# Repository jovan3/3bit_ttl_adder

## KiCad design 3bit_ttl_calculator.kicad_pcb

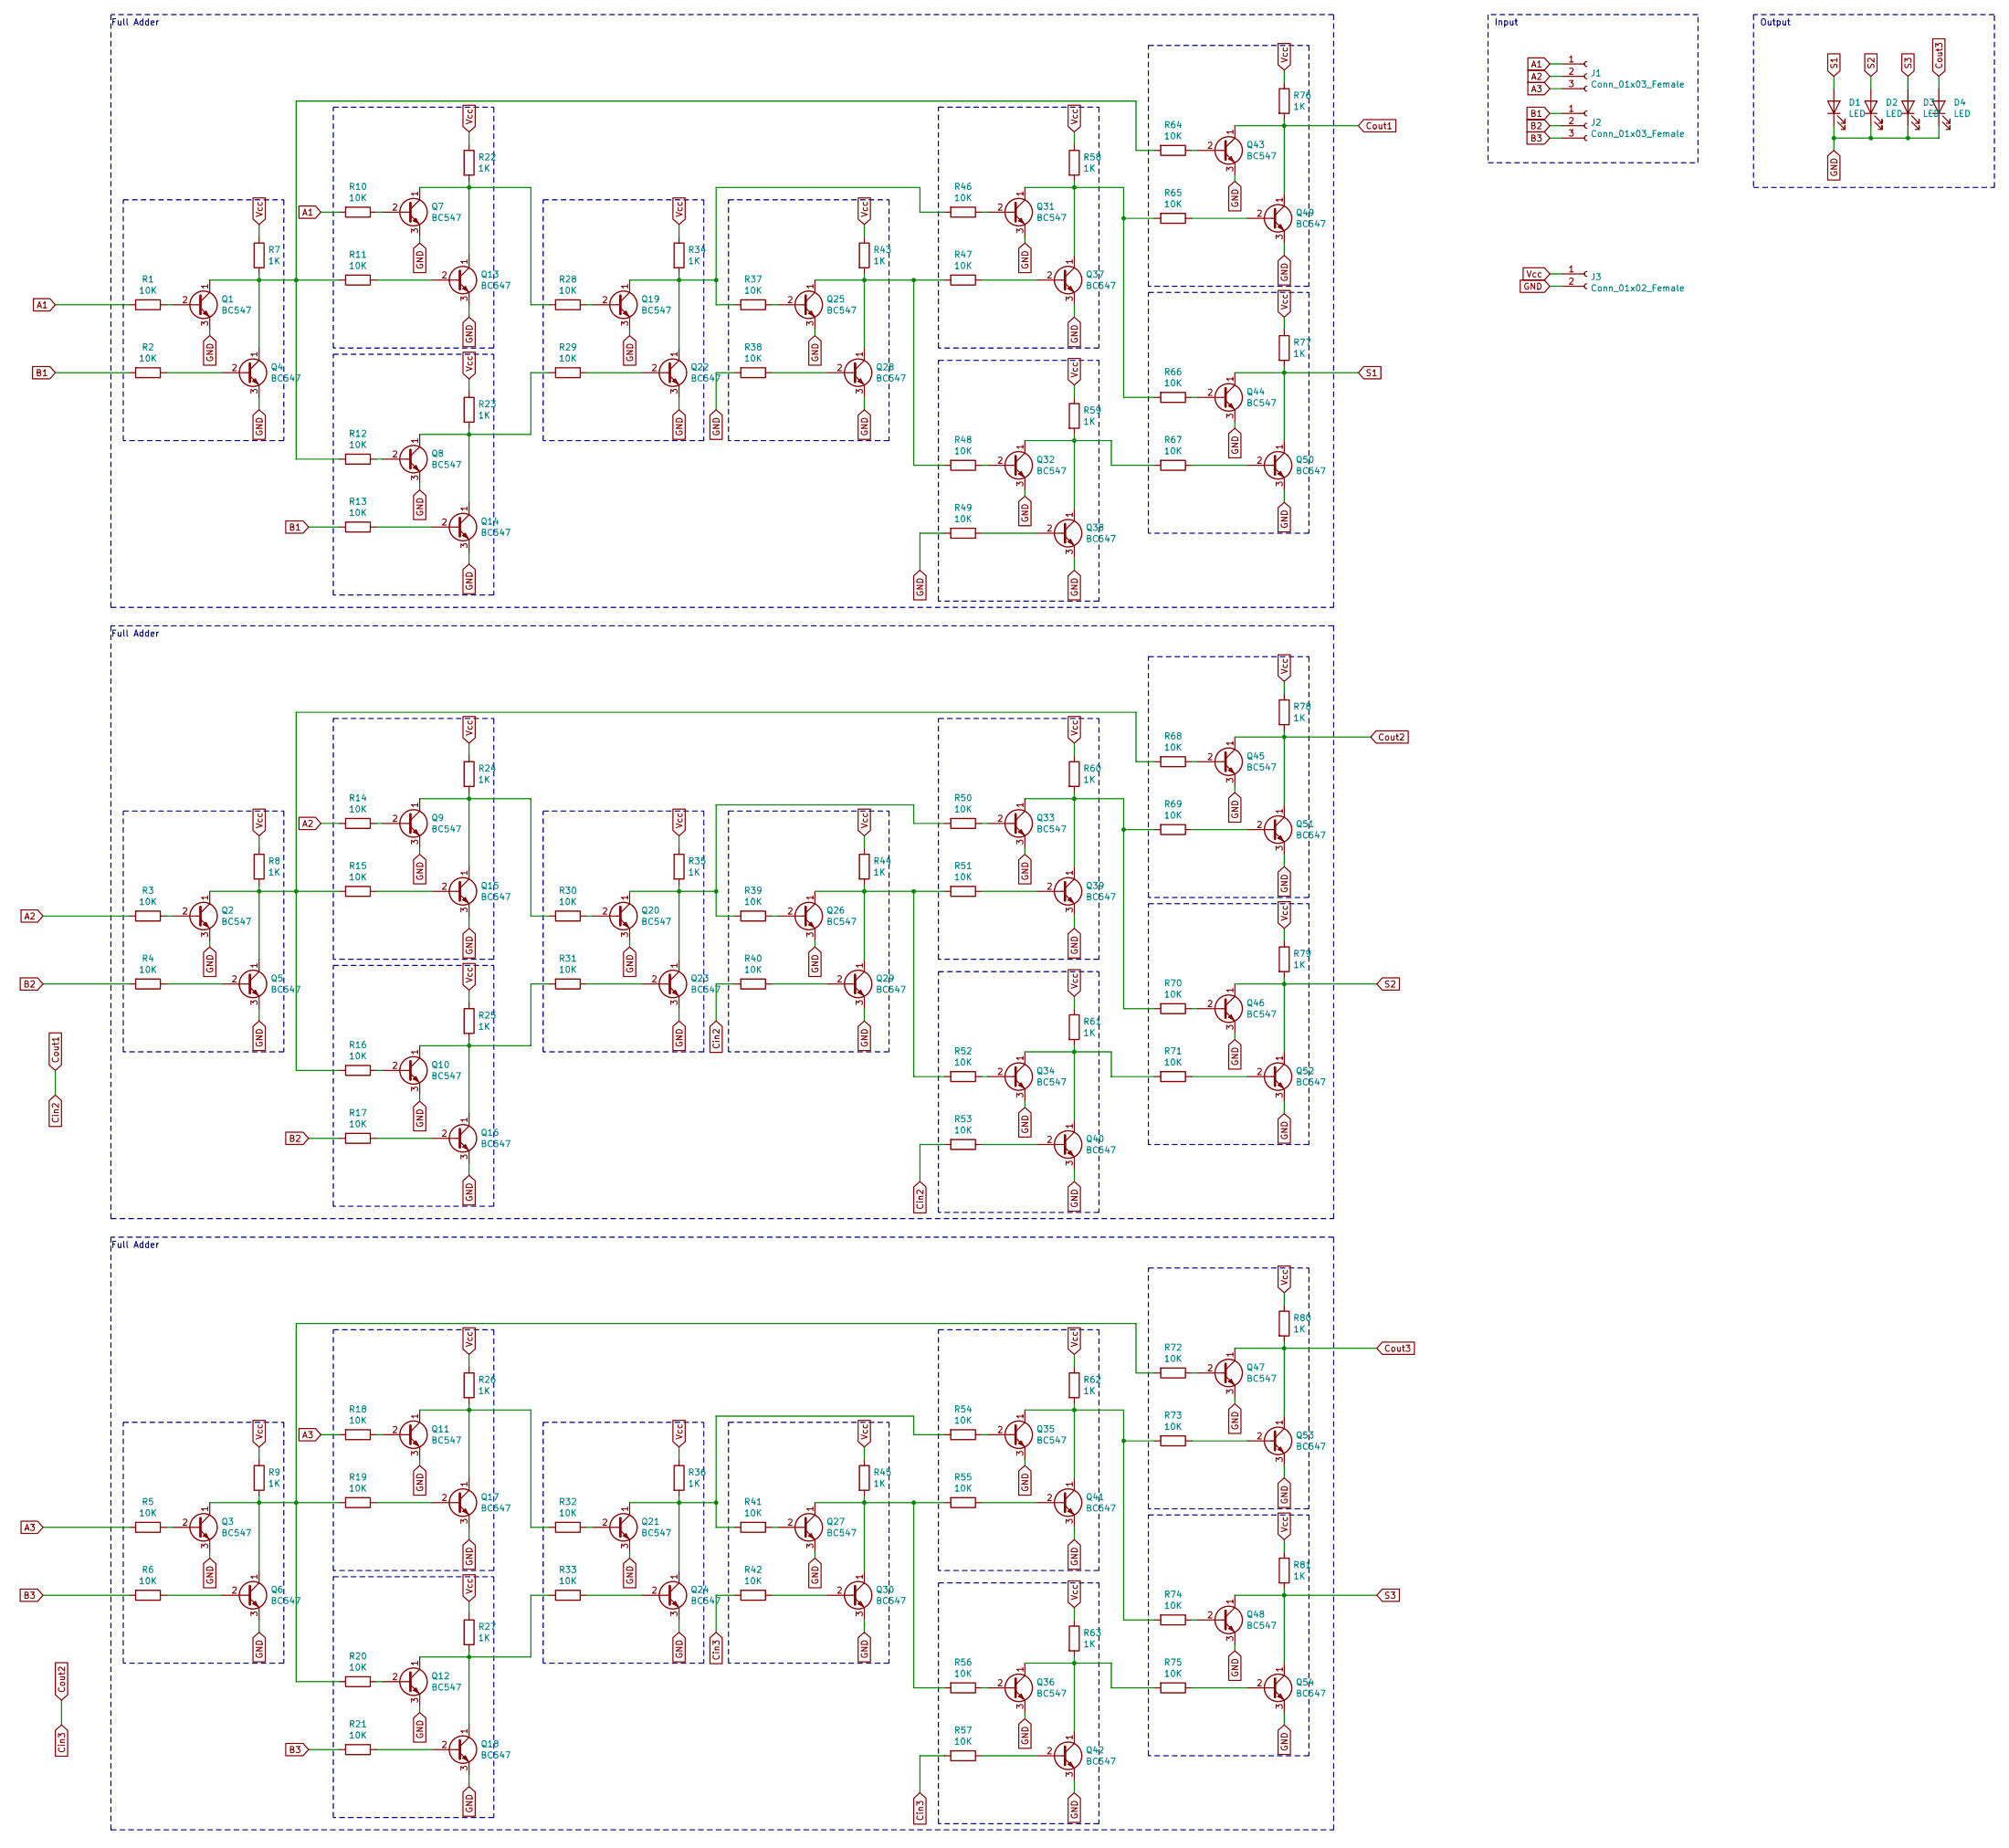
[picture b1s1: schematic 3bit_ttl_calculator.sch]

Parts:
D1, D2, D3, D4: LED; LED_D3.0mm
J1, J2: Conn_01x03_Female; PinHeader_1x03_P2.54mm_Vertical
J3: Conn_01x02_Female; PinHeader_1x02_P2.54mm_Vertical
Q1, Q2, Q3, Q4, Q5, Q6, Q7, Q8, Q9, Q10, Q11, Q12, Q13, Q14, Q15, Q16, Q17, Q18, Q19, Q20, Q21, Q22, Q23, Q24, Q25, Q26, Q27, Q28, Q29, Q30, Q31, Q32, Q33, Q34, Q35, Q36, Q37, Q38, Q39, Q40, Q41, Q42, Q43, Q44, Q45, Q46, Q47, Q48, Q49, Q50, Q51, Q52, Q53, Q54: BC547; TO-92_Inline
R1, R2, R3, R4, R5, R6, R10, R11, R12, R13, R14, R15, R16, R17, R18, R19, R20, R21, R28, R29, R30, R31, R32, R33, R37, R38, R39, R40, R41, R42, R46, R47, R48, R49, R50, R51, R52, R53, R54, R55, R56, R57, R64, R65, R66, R67, R68, R69, R70, R71, R72, R73, R74, R75: 10K; R_Axial_DIN0207_L6.3mm_D2.5mm_P10.16mm_Horizontal
R7, R8, R9, R22, R23, R24, R25, R26, R27, R34, R35, R36, R43, R44, R45, R58, R59, R60, R61, R62, R63, R76, R77, R78, R79, R80, R81: 1K; R_Axial_DIN0207_L6.3mm_D2.5mm_P10.16mm_Horizontal

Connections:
A1: J1.1, R1.2, R10.2
A2: J1.2, R3.2, R14.2
A3: J1.3, R5.2, R18.2
B1: J2.1, R2.2, R13.2
B2: J2.2, R4.2, R17.2
B3: J2.3, R6.2, R21.2
Cin2: Q43.1 (C), Q49.1 (C), R40.2, R53.2, R76.2
Cin3: Q45.1 (C), Q51.1 (C), R42.2, R57.2, R78.2
Cout3: D4.2 (A), Q47.1 (C), Q53.1 (C), R80.2
GND: D1.1 (K), D2.1 (K), D3.1 (K), D4.1 (K), J3.2, Q1.3 (E), Q2.3 (E), Q3.3 (E), Q4.3 (E), Q5.3 (E), Q6.3 (E), Q7.3 (E), Q8.3 (E), Q9.3 (E), Q10.3 (E), Q11.3 (E), Q12.3 (E), Q13.3 (E), Q14.3 (E), Q15.3 (E), Q16.3 (E), Q17.3 (E), Q18.3 (E), Q19.3 (E), Q20.3 (E), Q21.3 (E), Q22.3 (E), Q23.3 (E), Q24.3 (E), Q25.3 (E), Q26.3 (E), Q27.3 (E), Q28.3 (E), Q29.3 (E), Q30.3 (E), Q31.3 (E), Q32.3 (E), Q33.3 (E), Q34.3 (E), Q35.3 (E), Q36.3 (E), Q37.3 (E), Q38.3 (E), Q39.3 (E), Q40.3 (E), Q41.3 (E), Q42.3 (E), Q43.3 (E), Q44.3 (E), Q45.3 (E), Q46.3 (E), Q47.3 (E), Q48.3 (E), Q49.3 (E), Q50.3 (E), Q51.3 (E), Q52.3 (E), Q53.3 (E), Q54.3 (E), R38.2, R49.2
unnamed: Q1.1 (C), Q4.1 (C), R7.2, R11.2, R12.2, R64.2
unnamed: Q1.2 (B), R1.1
unnamed: Q2.1 (C), Q5.1 (C), R8.2, R15.2, R16.2, R68.2
unnamed: Q2.2 (B), R3.1
unnamed: Q3.1 (C), Q6.1 (C), R9.2, R19.2, R20.2, R72.2
unnamed: Q3.2 (B), R5.1
unnamed: Q4.2 (B), R2.1
unnamed: Q5.2 (B), R4.1
unnamed: Q6.2 (B), R6.1
unnamed: Q7.2 (B), R10.1
unnamed: Q8.2 (B), R12.1
unnamed: Q9.2 (B), R14.1
unnamed: Q10.1 (C), Q16.1 (C), R25.2, R31.2
unnamed: Q10.2 (B), R16.1
unnamed: Q11.1 (C), Q17.1 (C), R26.2, R32.2
unnamed: Q11.2 (B), R18.1
unnamed: Q12.1 (C), Q18.1 (C), R27.2, R33.2
unnamed: Q12.2 (B), R20.1
unnamed: Q7.1 (C), Q13.1 (C), R22.2, R28.2
unnamed: Q13.2 (B), R11.1
unnamed: Q8.1 (C), Q14.1 (C), R23.2, R29.2
unnamed: Q14.2 (B), R13.1
unnamed: Q9.1 (C), Q15.1 (C), R24.2, R30.2
unnamed: Q15.2 (B), R15.1
unnamed: Q16.2 (B), R17.1
unnamed: Q17.2 (B), R19.1
unnamed: Q18.2 (B), R21.1
unnamed: Q19.1 (C), Q22.1 (C), R34.2, R37.2, R46.2
unnamed: Q19.2 (B), R28.1
unnamed: Q20.1 (C), Q23.1 (C), R35.2, R39.2, R50.2
unnamed: Q20.2 (B), R30.1
unnamed: Q21.1 (C), Q24.1 (C), R36.2, R41.2, R54.2
unnamed: Q21.2 (B), R32.1
unnamed: Q22.2 (B), R29.1
unnamed: Q23.2 (B), R31.1
unnamed: Q24.2 (B), R33.1
unnamed: Q25.1 (C), Q28.1 (C), R43.2, R47.2, R48.2
unnamed: Q25.2 (B), R37.1
unnamed: Q26.1 (C), Q29.1 (C), R44.2, R51.2, R52.2
unnamed: Q26.2 (B), R39.1
unnamed: Q27.1 (C), Q30.1 (C), R45.2, R55.2, R56.2
unnamed: Q27.2 (B), R41.1
unnamed: Q28.2 (B), R38.1
unnamed: Q29.2 (B), R40.1
unnamed: Q30.2 (B), R42.1
unnamed: Q31.1 (C), Q37.1 (C), R58.2, R65.2, R66.2
unnamed: Q31.2 (B), R46.1
unnamed: Q32.1 (C), Q38.1 (C), R59.2, R67.2
unnamed: Q32.2 (B), R48.1
unnamed: Q33.1 (C), Q39.1 (C), R60.2, R69.2, R70.2
unnamed: Q33.2 (B), R50.1
unnamed: Q34.1 (C), Q40.1 (C), R61.2, R71.2
unnamed: Q34.2 (B), R52.1
unnamed: Q35.1 (C), Q41.1 (C), R62.2, R73.2, R74.2
unnamed: Q35.2 (B), R54.1
unnamed: Q36.1 (C), Q42.1 (C), R63.2, R75.2
unnamed: Q36.2 (B), R56.1
unnamed: Q37.2 (B), R47.1
unnamed: Q38.2 (B), R49.1
unnamed: Q39.2 (B), R51.1
unnamed: Q40.2 (B), R53.1
unnamed: Q41.2 (B), R55.1
unnamed: Q42.2 (B), R57.1
unnamed: Q43.2 (B), R64.1
unnamed: Q44.2 (B), R66.1
unnamed: Q45.2 (B), R68.1
unnamed: Q46.2 (B), R70.1
unnamed: Q47.2 (B), R72.1
unnamed: Q48.2 (B), R74.1
unnamed: Q49.2 (B), R65.1
unnamed: Q50.2 (B), R67.1
unnamed: Q51.2 (B), R69.1
unnamed: Q52.2 (B), R71.1
unnamed: Q53.2 (B), R73.1
unnamed: Q54.2 (B), R75.1
S1: D1.2 (A), Q44.1 (C), Q50.1 (C), R77.2
S2: D2.2 (A), Q46.1 (C), Q52.1 (C), R79.2
S3: D3.2 (A), Q48.1 (C), Q54.1 (C), R81.2
Vcc: J3.1, R7.1, R8.1, R9.1, R22.1, R23.1, R24.1, R25.1, R26.1, R27.1, R34.1, R35.1, R36.1, R43.1, R44.1, R45.1, R58.1, R59.1, R60.1, R61.1, R62.1, R63.1, R76.1, R77.1, R78.1, R79.1, R80.1, R81.1

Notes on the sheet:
Full Adder
Output
Input

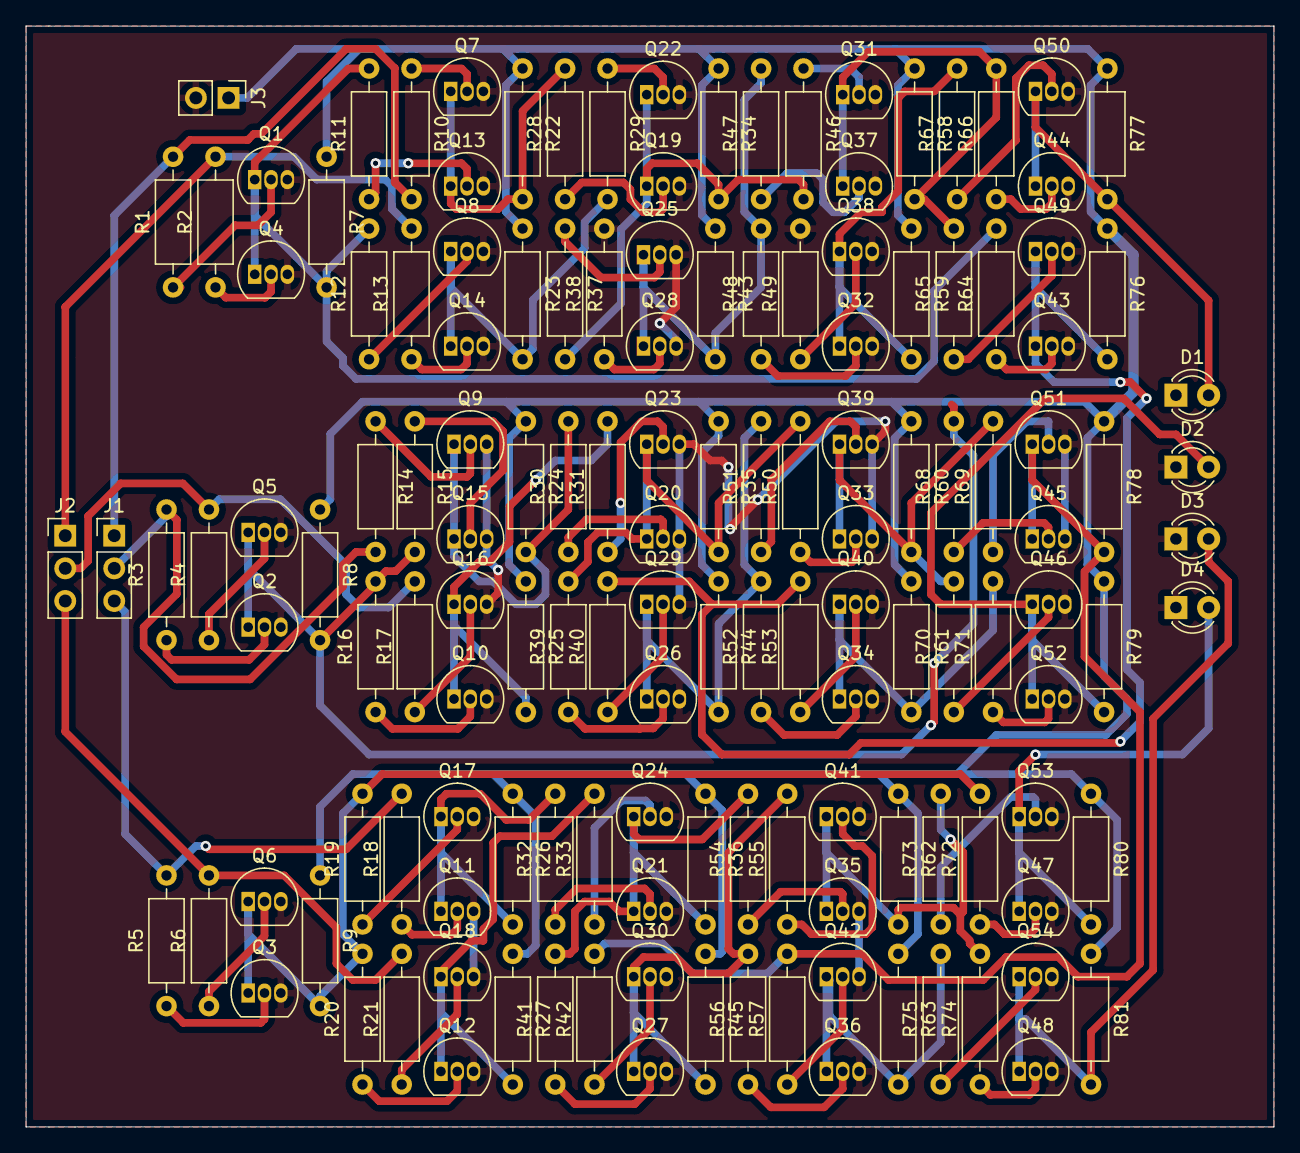
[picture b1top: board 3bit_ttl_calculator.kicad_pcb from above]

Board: 2 copper layers, 97.0 x 85.6 mm, 142 parts (0 on the bottom side), 89 nets.

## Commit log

2020-04-25 fix labels. add input/output components
2020-04-26 fix schematics, add board design...
